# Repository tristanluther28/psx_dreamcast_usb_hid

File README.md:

# PlayStation & Dreamcast USB Gamepad

Check out my website for more details: https://tristanluther.com/1/33

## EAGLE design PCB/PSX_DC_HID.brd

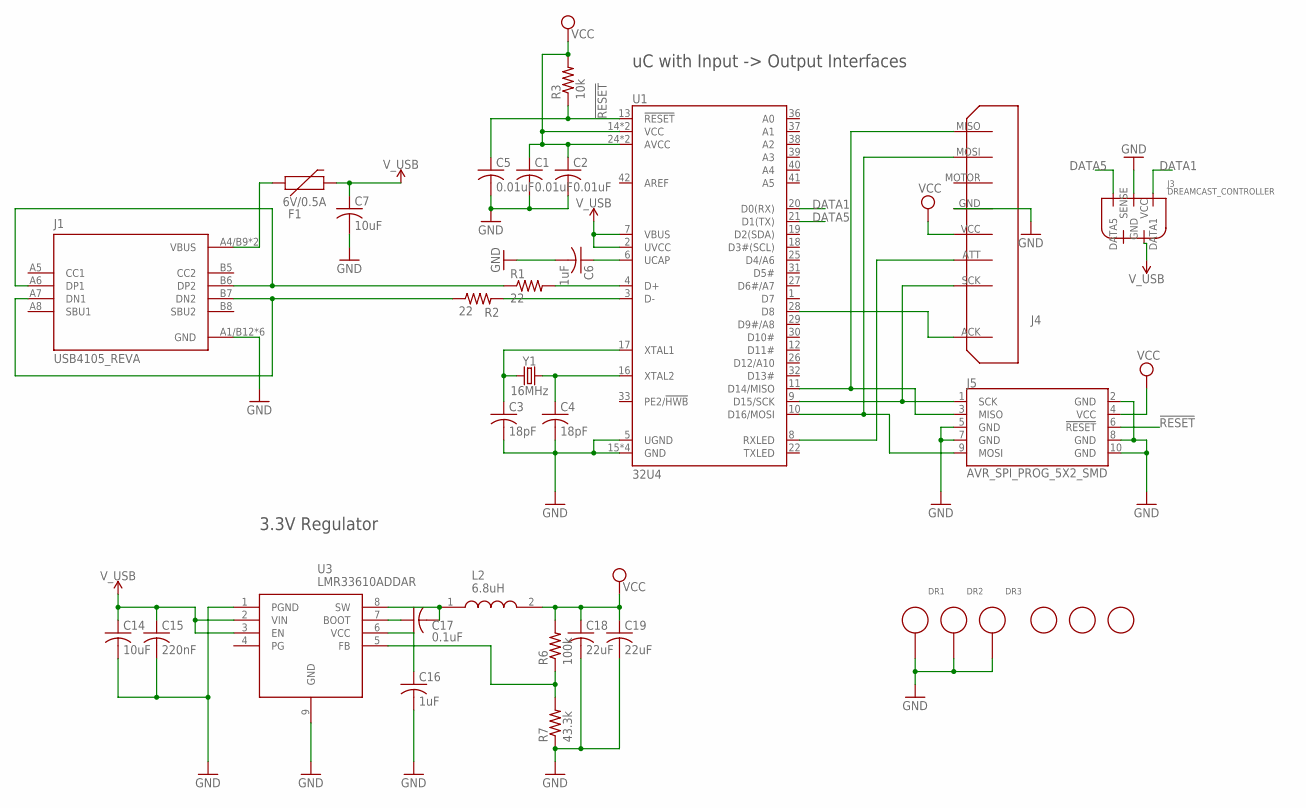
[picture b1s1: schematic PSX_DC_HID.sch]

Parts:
C1, C2, C5: 0.01uF; C0805
C3, C4: 18pF; C0805
C6, C16: 1uF; C0805
C7, C14: 10uF; C0805
C15: 220nF; C0805
C17: 0.1uF; C0805
C18, C19: 22uF; C0805
DR1, DR2, DR3: 3MM_DRILL_GND
F1: 6V/0.5A; 1206
J1: USB4105_REVA; GCT_USB4105_REVA
J3: DREAMCAST_CONTROLLER; 1_05X2MM
J4: PSX_CONTROLLERPSX_HORIZONTAL; PSX_HORIZONTAL
J5: AVR_SPI_PROG_5X2_SMD; SAMTECH_FTSH-105-01
L2: 6.8uH; INDPM5752X150N
R1, R2: 22; R0805
R3: 10k; R0805
R6: 100k; R0805
R7: 43.3k; R0805
U1: 32U4; TQFP44
U3: LMR33610ADDAR; SOIC127P600X170-9N
U$2, U$3, U$4: FIDUCIAL; FIDUCIAL_1MM
Y1: 16MHz; CRYSTAL-SMD-5X3.2-4PAD

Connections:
!RESET: C5.1, J5.6 (!RESET), R3.1, U1.13 (!RESET)
DATA1: J3.1 (DATA1), U1.20 (D0(RX))
DATA5: J3.2 (DATA5), U1.21 (D1(TX))
GND: C1.2, C2.2, C3.2, C4.2, C5.2, C6.2, C7.2, C14.2, C15.2, C16.2, C18.2, C19.2, DR1.DR, DR2.DR, DR3.DR, J1.A1/B12 (GND), J1.B1/A12 (GND), J1.G1 (GND), J1.G2 (GND), J1.G3 (GND), J1.G4 (GND), J3.3 (GND), J4.GND, J5.2 (GND), J5.5 (GND), J5.7 (GND), J5.8 (GND), J5.10 (GND), R7.1, U1.5 (UGND), U1.15 (GND), U1.23 (GND), U1.35 (GND), U1.43 (GND), U3.1 (PGND), U3.9 (GND)
unnamed: C4.1, U1.16 (XTAL2), Y1.3 (2)
unnamed: C3.1, U1.17 (XTAL1), Y1.1
unnamed: R2.2, U1.3 (D-)
unnamed: R1.2, U1.4 (D+)
unnamed: J1.A7 (DN1), J1.B7 (DN2), R2.1
unnamed: J4.MISO, J5.3 (MISO), U1.11 (D14/MISO)
unnamed: J4.SCK, J5.1 (SCK), U1.9 (D15/SCK)
unnamed: J4.MOSI, J5.9 (MOSI), U1.10 (D16/MOSI)
unnamed: C6.1, U1.6 (UCAP)
unnamed: J4.ATT, U1.8 (RXLED)
unnamed: J1.A6 (DP1), J1.B6 (DP2), R1.1
unnamed: J4.ACK, U1.28 (D8)
unnamed: F1.1, J1.A4/B9 (VBUS), J1.B4/A9 (VBUS)
unnamed: R6.1, R7.2, U3.5 (FB)
unnamed: C17.2, L2.1, U3.8 (SW)
unnamed: C17.1, U3.7 (BOOT)
unnamed: C16.1, U3.6 (VCC)
VCC: C1.1, C2.1, C18.1, C19.1, J4.VCC, J5.4 (VCC), L2.2, R3.2, R6.2, U1.14 (VCC), U1.24 (AVCC), U1.34 (VCC), U1.44 (AVCC)
V_USB: C7.1, C14.1, C15.1, F1.2, J3.5 (VCC), U1.2 (UVCC), U1.7 (VBUS), U3.2 (VIN), U3.3 (EN)

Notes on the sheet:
uC with Input -> Output Interfaces
3.3V Regulator

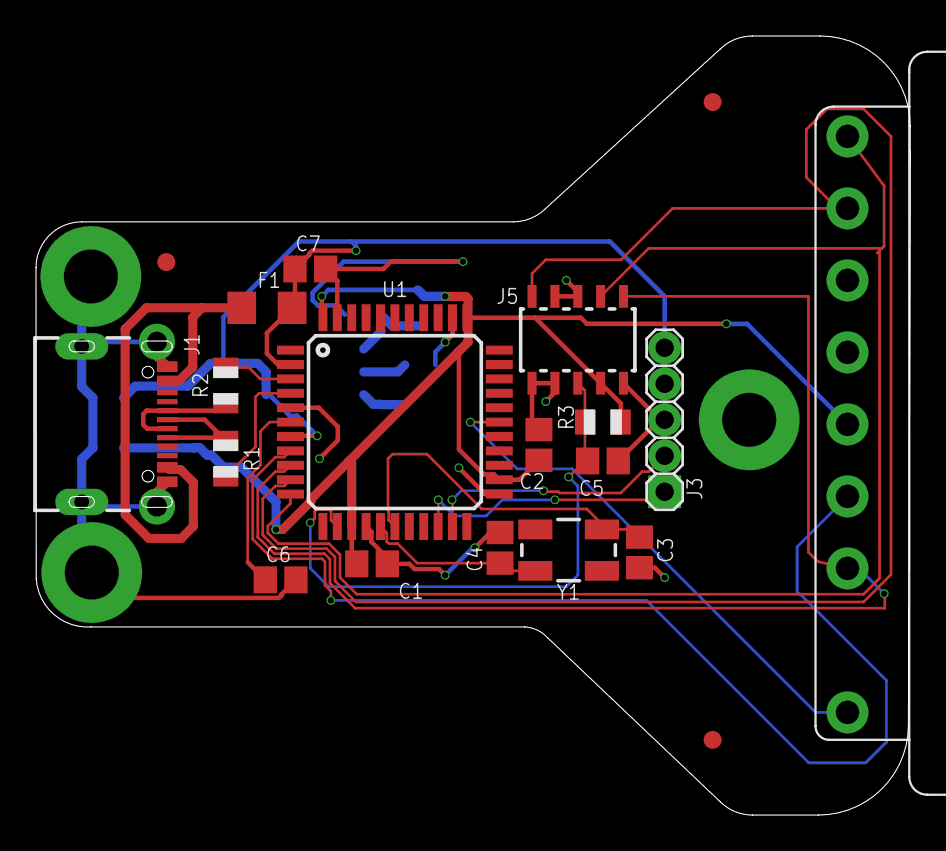
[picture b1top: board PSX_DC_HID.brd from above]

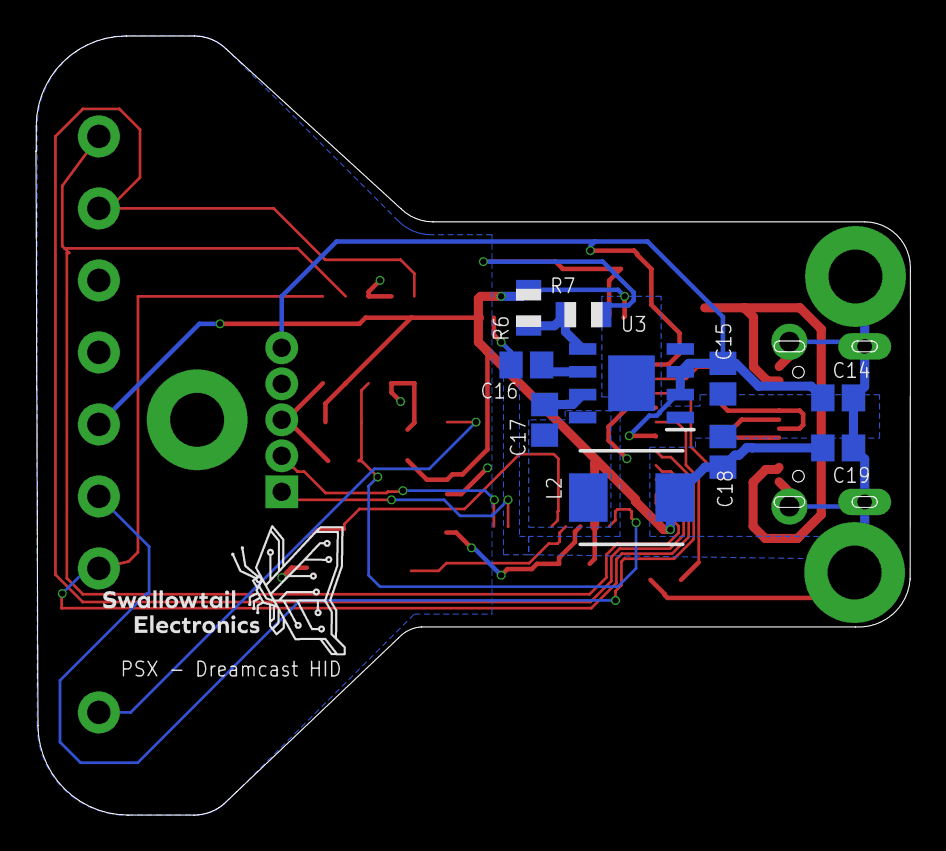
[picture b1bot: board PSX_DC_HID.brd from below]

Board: 2 copper layers, 48.6 x 43.3 mm, 34 parts (11 on the bottom side), 23 nets.

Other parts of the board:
U$5: SWALLOWTAIL_LOGO_SMALL

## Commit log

2021-08-06 Initial commit
    Getting everything in one spot
2021-08-06 Update README.md
    A quick description
2023-07-07 Update README.md Website URL

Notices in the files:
parts and their libraries:
SparkFun-PowerSymbols: Licensing: Creative Commons ShareAlike 4.0 International - https://creativecommons.org/licenses/by-sa/4.0
